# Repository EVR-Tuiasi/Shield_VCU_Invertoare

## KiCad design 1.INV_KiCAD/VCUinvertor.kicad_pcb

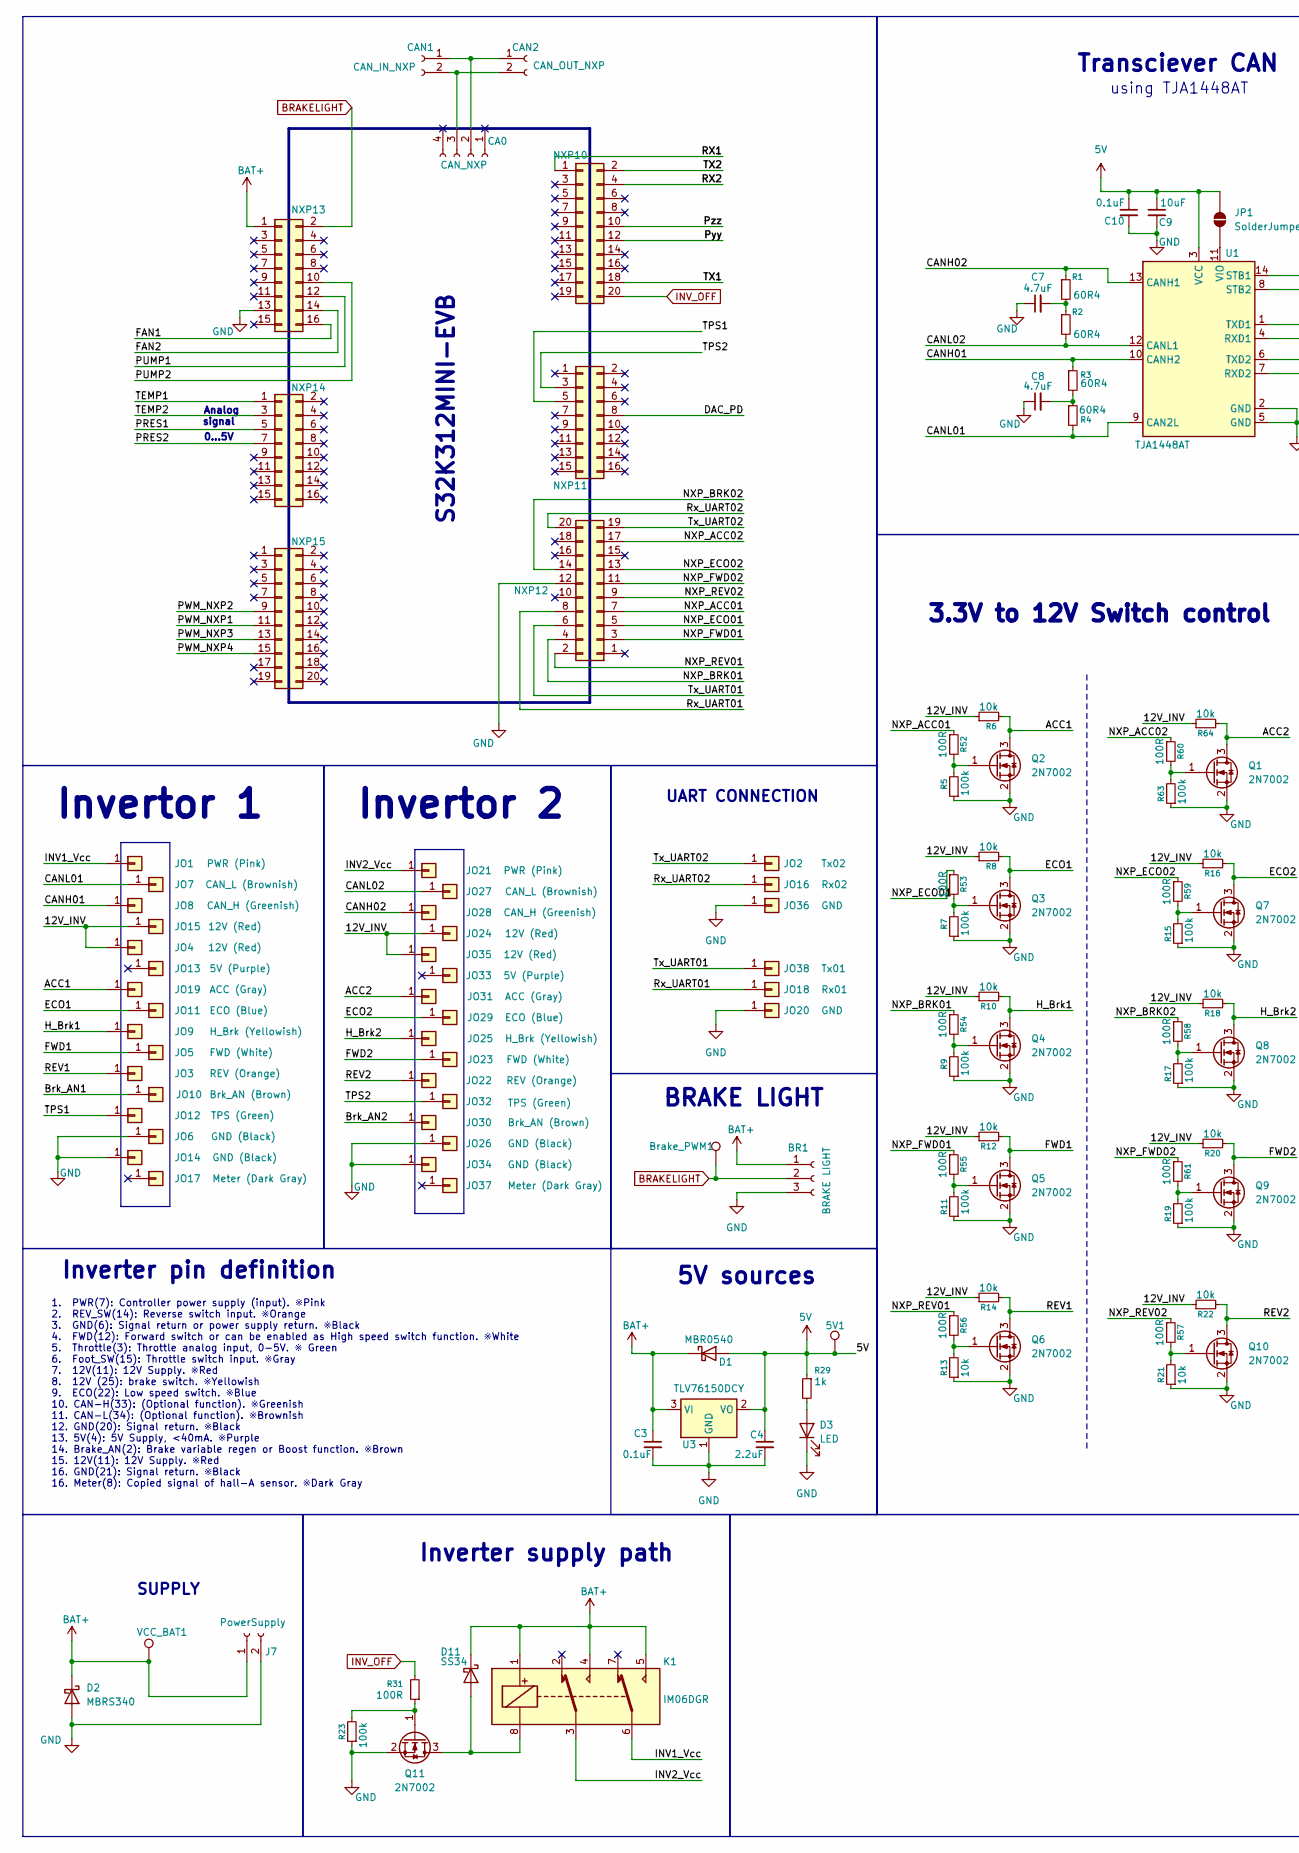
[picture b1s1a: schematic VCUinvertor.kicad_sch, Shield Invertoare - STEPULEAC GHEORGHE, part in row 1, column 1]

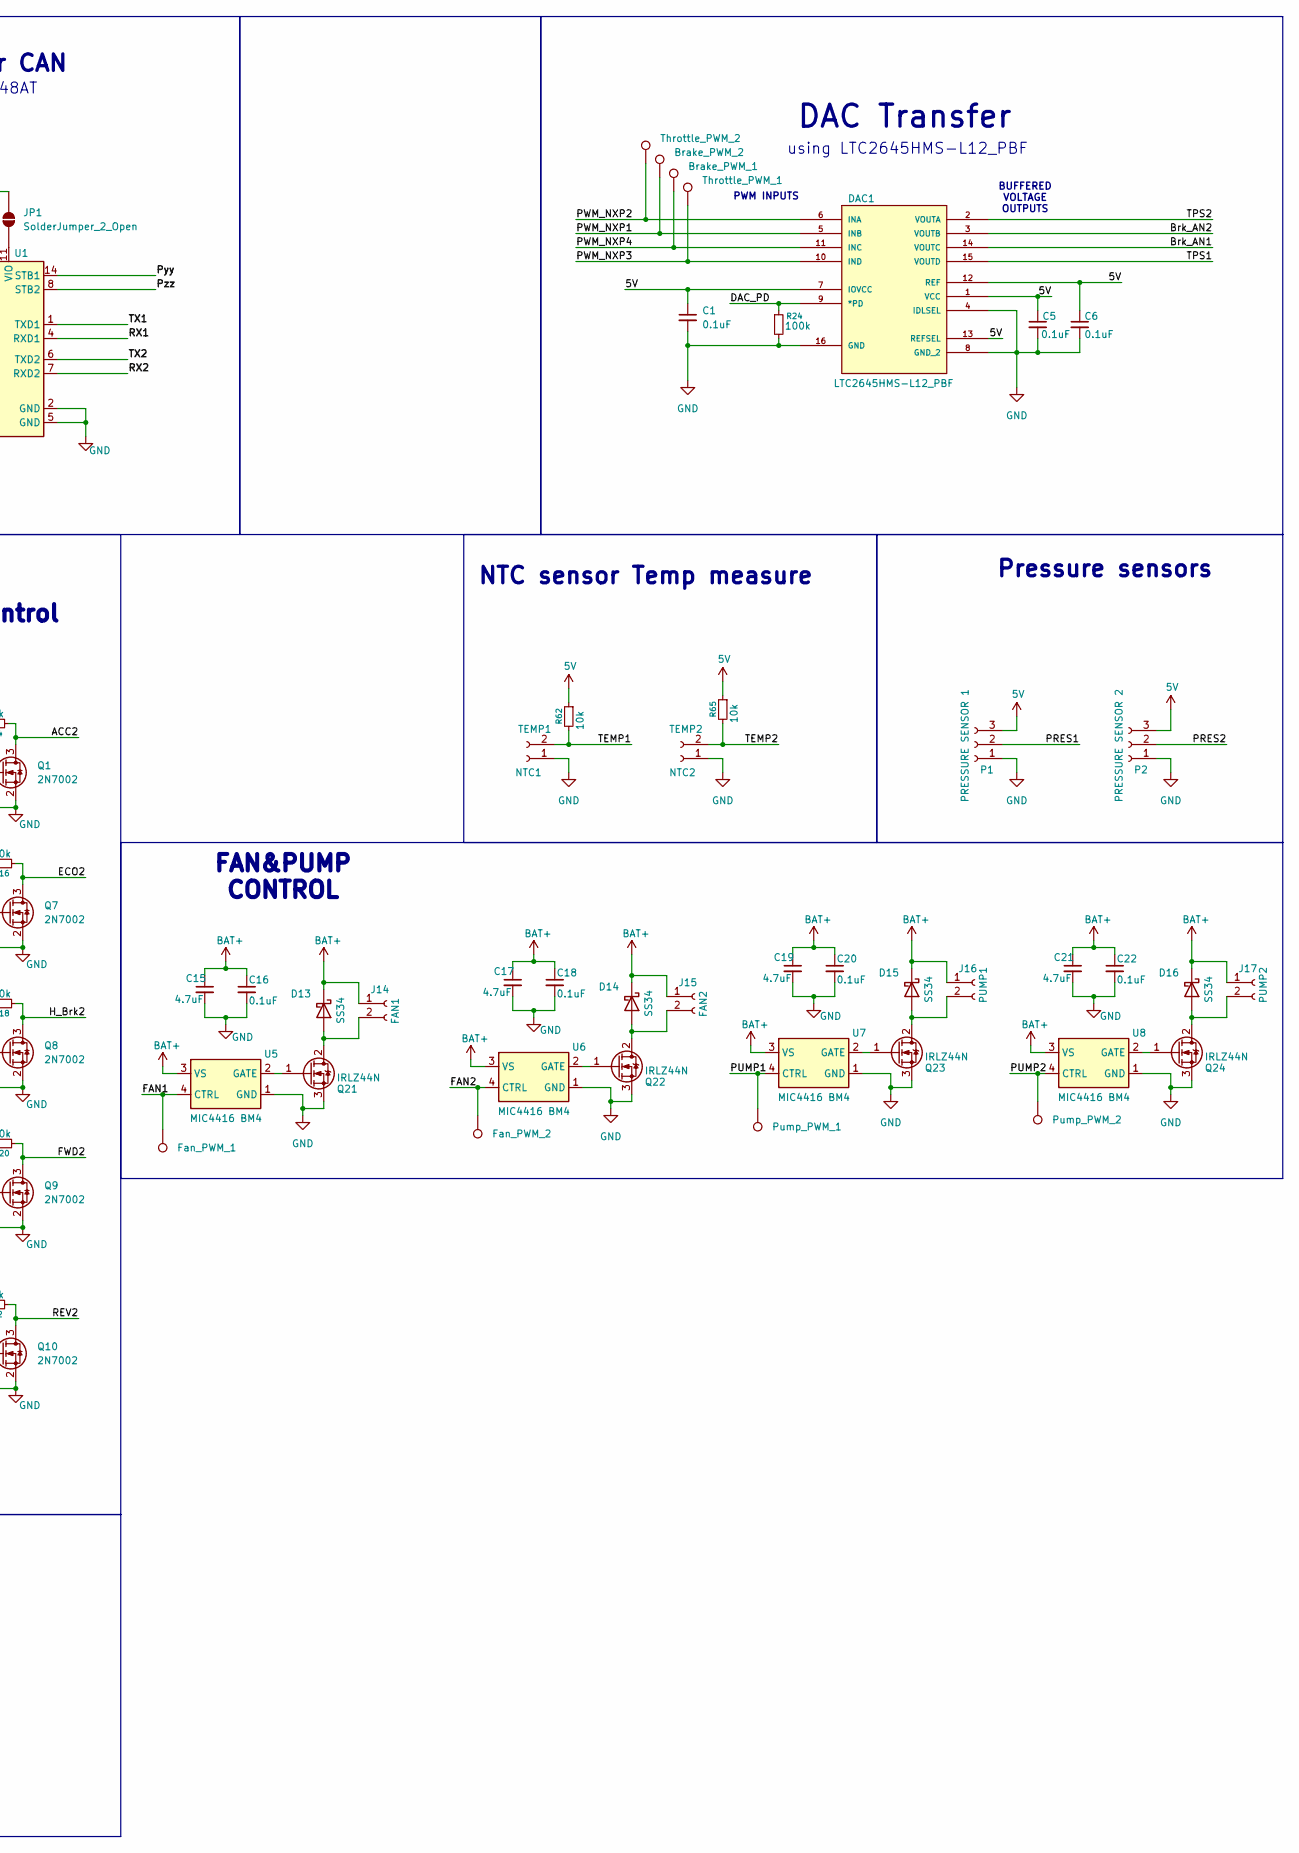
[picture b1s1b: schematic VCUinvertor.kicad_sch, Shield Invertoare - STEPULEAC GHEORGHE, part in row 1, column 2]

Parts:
5V1: 5V; TestPoint_Pad_D1.5mm
BR1: BRAKE LIGHT; JST_XH_B3B-XH-A_1x03_P2.50mm_Vertical
Brake_PWM1: TestPoint; TestPoint_Pad_D1.5mm
Brake_PWM_1, Brake_PWM_2: TestPoint; TestPoint_Pad_D1.5mm
C1, C3, C5, C6, C10, C16, C18, C20, C22: 0.1uF; C_1206_3216Metric_Pad1.33x1.80mm_HandSolder
C4: 2.2uF; C_1206_3216Metric_Pad1.33x1.80mm_HandSolder
C7, C8, C15, C17, C19, C21: 4.7uF; C_1206_3216Metric_Pad1.33x1.80mm_HandSolder
C9: 10uF; C_1206_3216Metric_Pad1.33x1.80mm_HandSolder
CA0: CAN_NXP; PinHeader_1x04_P2.54mm_Vertical
CAN1: CAN_IN_NXP; JST_PH_B2B-PH-K_1x02_P2.00mm_Vertical
CAN2: CAN_OUT_NXP; JST_PH_B2B-PH-K_1x02_P2.00mm_Vertical
D1: MBR0540; D_SOD-123
D2: MBRS340; D_SMC
D3: LED; LED_0805_2012Metric_Pad1.15x1.40mm_HandSolder
D11, D13, D14, D15, D16: SS34; D_SMA
DAC1: LTC2645HMS-L12_PBF; MSOP-16_MS; MANUFACTURER_PART_NUMBER ltc2645imsl8#pbf
Fan_PWM_1, Fan_PWM_2: TestPoint; TestPoint_Pad_D1.5mm
J7: PowerSupply; PhoenixContact_GMSTBVA_2,5_2-G-7,62_1x02_P7.62mm_Vertical
J14: FAN1; JST_XH_B2B-XH-A_1x02_P2.50mm_Vertical
J15: FAN2; JST_XH_B2B-XH-A_1x02_P2.50mm_Vertical
J16: PUMP1; JST_XH_B2B-XH-A_1x02_P2.50mm_Vertical
J17: PUMP2; JST_XH_B2B-XH-A_1x02_P2.50mm_Vertical
JO1, JO21: PWR (Pink); SolderWire-0.75sqmm_1x01_D1.25mm_OD2.3mm
JO2: Tx02; SolderWire-0.5sqmm_1x01_D0.9mm_OD2.1mm
JO3, JO22: REV (Orange); SolderWire-0.75sqmm_1x01_D1.25mm_OD2.3mm
JO4, JO15, JO24, JO35: 12V (Red); SolderWire-0.75sqmm_1x01_D1.25mm_OD2.3mm
JO5, JO23: FWD (White); SolderWire-0.75sqmm_1x01_D1.25mm_OD2.3mm
JO6, JO14, JO26, JO34: GND (Black); SolderWire-0.75sqmm_1x01_D1.25mm_OD2.3mm
JO7, JO27: CAN_L (Brownish); SolderWire-0.75sqmm_1x01_D1.25mm_OD2.3mm
JO8, JO28: CAN_H (Greenish); SolderWire-0.75sqmm_1x01_D1.25mm_OD2.3mm
JO9, JO25: H_Brk (Yellowish); SolderWire-0.75sqmm_1x01_D1.25mm_OD2.3mm
JO10, JO30: Brk_AN (Brown); SolderWire-0.75sqmm_1x01_D1.25mm_OD2.3mm
JO11, JO29: ECO (Blue); SolderWire-0.75sqmm_1x01_D1.25mm_OD2.3mm
JO12, JO32: TPS (Green); SolderWire-0.75sqmm_1x01_D1.25mm_OD2.3mm
JO13, JO33: 5V (Purple); SolderWire-0.75sqmm_1x01_D1.25mm_OD2.3mm
JO16: Rx02; SolderWire-0.5sqmm_1x01_D0.9mm_OD2.1mm
JO17, JO37: Meter (Dark Gray); SolderWire-0.75sqmm_1x01_D1.25mm_OD2.3mm
JO18: Rx01; SolderWire-0.5sqmm_1x01_D0.9mm_OD2.1mm
JO19, JO31: ACC (Gray); SolderWire-0.75sqmm_1x01_D1.25mm_OD2.3mm
JO20, JO36: GND; SolderWire-0.5sqmm_1x01_D0.9mm_OD2.1mm
JO38: Tx01; SolderWire-0.5sqmm_1x01_D0.9mm_OD2.1mm
JP1: SolderJumper_2_Open; SolderJumper-2_P1.3mm_Open_RoundedPad1.0x1.5mm
K1: IM06DGR; Relay_IM06DGR
NXP10: NXP10; PinHeader_2x10_P2.54mm_Vertical
NXP11: NXP11; PinHeader_2x08_P2.54mm_Vertical
NXP12: NXP12; PinHeader_2x10_P2.54mm_Vertical
NXP13: NXP13; PinHeader_2x08_P2.54mm_Vertical
NXP14: NXP14; PinHeader_2x08_P2.54mm_Vertical
NXP15: NXP15; PinHeader_2x10_P2.54mm_Vertical
P1: PRESSURE SENSOR 1; JST_PH_B3B-PH-K_1x03_P2.00mm_Vertical
P2: PRESSURE SENSOR 2; JST_PH_B3B-PH-K_1x03_P2.00mm_Vertical
Pump_PWM_1, Pump_PWM_2: TestPoint; TestPoint_Pad_D1.5mm
Q1, Q2, Q3, Q4, Q5, Q6, Q7, Q8, Q9, Q10, Q11: 2N7002; SOT-23
Q21, Q22, Q23, Q24: IRLZ44N; TO-220-3_Vertical
R1, R2, R3, R4: 60R4; R_1206_3216Metric_Pad1.30x1.75mm_HandSolder
R5, R7, R9, R11, R15, R17, R19, R23, R24, R63: 100k; R_1206_3216Metric_Pad1.30x1.75mm_HandSolder
R6, R8, R10, R12, R13, R14, R16, R18, R20, R21, R22, R62, R64, R65: 10k; R_1206_3216Metric_Pad1.30x1.75mm_HandSolder
R29: 1k; R_1206_3216Metric_Pad1.30x1.75mm_HandSolder
R31, R52, R53, R54, R55, R56, R57, R58, R59, R60, R61: 100R; R_1206_3216Metric_Pad1.30x1.75mm_HandSolder
TEMP1: NTC1; JST_PH_B2B-PH-K_1x02_P2.00mm_Vertical
TEMP2: NTC2; JST_PH_B2B-PH-K_1x02_P2.00mm_Vertical
Throttle_PWM_1, Throttle_PWM_2: TestPoint; TestPoint_Pad_D1.5mm
U1: TJA1448AT; NXP-TJA1448A_NXP
U3: TLV76150DCY; SOT-223-3_TabPin2
U5, U6, U7, U8: MIC4416 BM4; SOT-143_Handsoldering
VCC_BAT1: 12V; TestPoint_Pad_D1.5mm

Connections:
5V: 5V1.1 (1_1), C1.1, C4.1, C5.1, C6.1, C9.1, C10.1, D1.2 (A), DAC1.1 (VCC), DAC1.7 (IOVCC), DAC1.12 (REF), DAC1.13 (REFSEL), JP1.2 (B), P1.3, P2.3, R29.1, R62.1, R65.1, U1.3 (VCC), U3.2 (VO)
/12V_INV: JO4.1 (Pin_1_1), JO15.1 (Pin_1_1), JO24.1 (Pin_1_1), JO35.1 (Pin_1_1), R6.1, R8.1, R10.1, R12.1, R14.1, R16.1, R18.1, R20.1, R22.1, R64.1
/ACC1: JO19.1 (Pin_1_1), Q2.3 (D), R6.2
/ACC2: JO31.1 (Pin_1_1), Q1.3 (D), R64.2
/Brk_AN1: DAC1.14 (VOUTC), JO10.1 (Pin_1_1)
/Brk_AN2: DAC1.3 (VOUTB), JO30.1 (Pin_1_1)
/CANH01: JO8.1 (Pin_1_1), R3.1, U1.10 (CANH2)
/CANH02: JO28.1 (Pin_1_1), R1.1, U1.13 (CANH1)
/CANL01: JO7.1 (Pin_1_1), R4.2, U1.9 (CAN2L)
/CANL02: JO27.1 (Pin_1_1), R2.2, U1.12 (CANL1)
/DAC_PD: DAC1.9 (*PD), NXP11.8, R24.1
/ECO1: JO11.1 (Pin_1_1), Q3.3 (D), R8.2
/ECO2: JO29.1 (Pin_1_1), Q7.3 (D), R16.2
/FAN1: Fan_PWM_1.1 (1_1), NXP13.16, U5.4 (CTRL)
/FAN2: Fan_PWM_2.1 (1_1), NXP13.14, U6.4 (CTRL)
/FWD1: JO5.1 (Pin_1_1), Q5.3 (D), R12.2
/FWD2: JO23.1 (Pin_1_1), Q9.3 (D), R20.2
/H_Brk1: JO9.1 (Pin_1_1), Q4.3 (D), R10.2
/H_Brk2: JO25.1 (Pin_1_1), Q8.3 (D), R18.2
/INV1_Vcc: JO1.1 (Pin_1_1), K1.6
/INV2_Vcc: JO21.1 (Pin_1_1), K1.3
/NXP_ACC01: NXP12.7, R52.1
/NXP_ACC02: NXP12.17, R60.1
/NXP_BRK01: NXP12.4, R54.1
/NXP_BRK02: NXP12.14, R58.1
/NXP_ECO01: NXP12.5, R53.1
/NXP_ECO02: NXP12.13, R59.1
/NXP_FWD01: NXP12.3, R55.1
/NXP_FWD02: NXP12.11, R61.1
/NXP_REV01: NXP12.2, R56.1
/NXP_REV02: NXP12.9, R57.1
/PRES1: NXP14.5, P1.2
/PRES2: NXP14.7, P2.2
/PUMP1: NXP13.12, Pump_PWM_1.1 (1_1), U7.4 (CTRL)
/PUMP2: NXP13.10, Pump_PWM_2.1 (1_1), U8.4 (CTRL)
/PWM_NXP1: Brake_PWM_2.1 (1_1), DAC1.5 (INB), NXP15.11
/PWM_NXP2: DAC1.6 (INA), NXP15.9, Throttle_PWM_2.1 (1_1)
/PWM_NXP3: DAC1.10 (IND), NXP15.13, Throttle_PWM_1.1 (1_1)
/PWM_NXP4: Brake_PWM_1.1 (1_1), DAC1.11 (INC), NXP15.15
/Pyy: NXP10.12, U1.14 (STB1)
/Pzz: NXP10.10, U1.8 (STB2)
/REV1: JO3.1 (Pin_1_1), Q6.3 (D), R14.2
/REV2: JO22.1 (Pin_1_1), Q10.3 (D), R22.2
/RX1: NXP10.1, U1.4 (RXD1)
/RX2: NXP10.4, U1.7 (RXD2)
/Rx_UART01: JO18.1 (Pin_1_1), NXP12.8
/Rx_UART02: JO16.1 (Pin_1_1), NXP12.20
/TEMP1: NXP14.1, R62.2, TEMP1.2
/TEMP2: NXP14.3, R65.2, TEMP2.2
/TPS1: DAC1.15 (VOUTD), JO12.1 (Pin_1_1), NXP11.5
/TPS2: DAC1.2 (VOUTA), JO32.1 (Pin_1_1), NXP11.3
/TX1: NXP10.18, U1.1 (TXD1)
/TX2: NXP10.2, U1.6 (TXD2)
/Tx_UART01: JO38.1 (Pin_1_1), NXP12.6
/Tx_UART02: JO2.1 (Pin_1_1), NXP12.19
BAT+: BR1.1, C3.1, C15.1, C16.1, C17.1, C18.1, C19.1, C20.1, C21.1, C22.1, D1.1 (K), D2.1 (K), D11.1 (K), D13.1 (K), D14.1 (K), D15.1 (K), D16.1 (K), J7.1, J14.1, J15.1, J16.1, J17.1, K1.1, K1.4, K1.5, NXP13.1, U3.3 (VI), U5.3 (VS), U6.3 (VS), U7.3 (VS), U8.3 (VS), VCC_BAT1.1 (1_1)
BRAKELIGHT: BR1.2, Brake_PWM1.1 (1_1), NXP13.2
GND: BR1.3, C1.2, C3.2, C4.2, C5.2, C6.2, C7.1, C8.1, C9.2, C10.2, C15.2, C16.2, C17.2, C18.2, C19.2, C20.2, C21.2, C22.2, D2.2 (A), D3.1 (K), DAC1.4 (IDLSEL), DAC1.8 (GND_2), DAC1.16 (GND), J7.2, JO6.1 (Pin_1_1), JO14.1 (Pin_1_1), JO20.1 (Pin_1_1), JO26.1 (Pin_1_1), JO34.1 (Pin_1_1), JO36.1 (Pin_1_1), NXP12.12, NXP13.13, P1.1, P2.1, Q1.2 (S), Q2.2 (S), Q3.2 (S), Q4.2 (S), Q5.2 (S), Q6.2 (S), Q7.2 (S), Q8.2 (S), Q9.2 (S), Q10.2 (S), Q11.2 (S), Q21.3 (S), Q22.3 (S), Q23.3 (S), Q24.3 (S), R5.1, R7.1, R9.1, R11.1, R13.1, R15.1, R17.1, R19.1, R21.1, R23.1, R24.2, R63.1, TEMP1.1, TEMP2.1, U1.2 (GND), U1.5 (GND), U3.1 (GND), U5.1 (GND), U6.1 (GND), U7.1 (GND), U8.1 (GND)
INV_OFF: NXP10.20, R31.2
unnamed: C7.2, R1.2, R2.1
unnamed: C8.2, R3.2, R4.1
unnamed: CA0.2, CAN1.1, CAN2.1
unnamed: CA0.3, CAN1.2, CAN2.2
unnamed: D3.2 (A), R29.2
unnamed: D11.2 (A), K1.8, Q11.3 (D)
unnamed: D13.2 (A), J14.2, Q21.2 (D)
unnamed: D14.2 (A), J15.2, Q22.2 (D)
unnamed: D15.2 (A), J16.2, Q23.2 (D)
unnamed: D16.2 (A), J17.2, Q24.2 (D)
unnamed: JP1.1 (A), U1.11 (VIO)
unnamed: Q1.1 (G), R60.2, R63.2
unnamed: Q2.1 (G), R5.2, R52.2
unnamed: Q3.1 (G), R7.2, R53.2
unnamed: Q4.1 (G), R9.2, R54.2
unnamed: Q5.1 (G), R11.2, R55.2
unnamed: Q6.1 (G), R13.2, R56.2
unnamed: Q7.1 (G), R15.2, R59.2
unnamed: Q8.1 (G), R17.2, R58.2
unnamed: Q9.1 (G), R19.2, R61.2
unnamed: Q10.1 (G), R21.2, R57.2
unnamed: Q11.1 (G), R23.2, R31.1
unnamed: Q21.1 (G), U5.2 (GATE)
unnamed: Q22.1 (G), U6.2 (GATE)
unnamed: Q23.1 (G), U7.2 (GATE)
unnamed: Q24.1 (G), U8.2 (GATE)

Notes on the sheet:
Transciever CAN
using LTC2645HMS-L12_PBF
NTC sensor Temp measure
UART CONNECTION
SUPPLY
FAN&PUMP CONTROL
3.3V to 12V Switch control
PWM INPUTS
BUFFERED VOLTAGE OUTPUTS
0...5V
Invertor 1
S32K312MINI-EVB
1. PWR(7): Controller power supply (input). ※Pink 2. REV_SW(14): Reverse switch input. ※Orange 3. GND(6): Signal return or power supply return. ※Black 4. FWD(12): Forward switch or can be enabled as High speed switch function. ※White 5. Throttle(3): Throttle analog input, 0-5V. ※ Green 6. Foot_SW(1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
Analog signal
Inverter supply path
Invertor 2
using TJA1448AT
Pressure sensors
5V sources
DAC Transfer
BRAKE LIGHT
Inverter pin definition

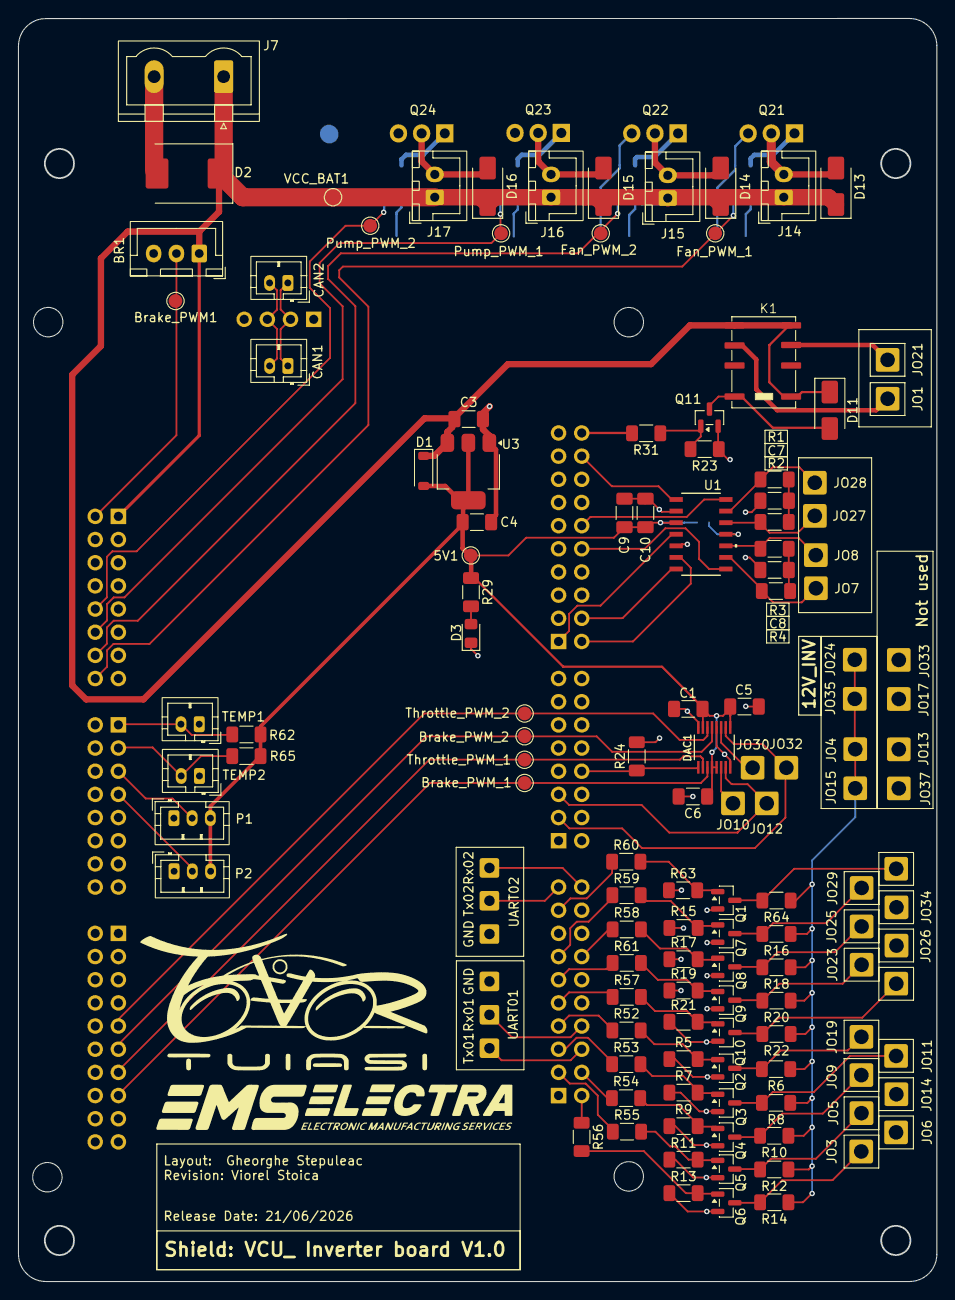
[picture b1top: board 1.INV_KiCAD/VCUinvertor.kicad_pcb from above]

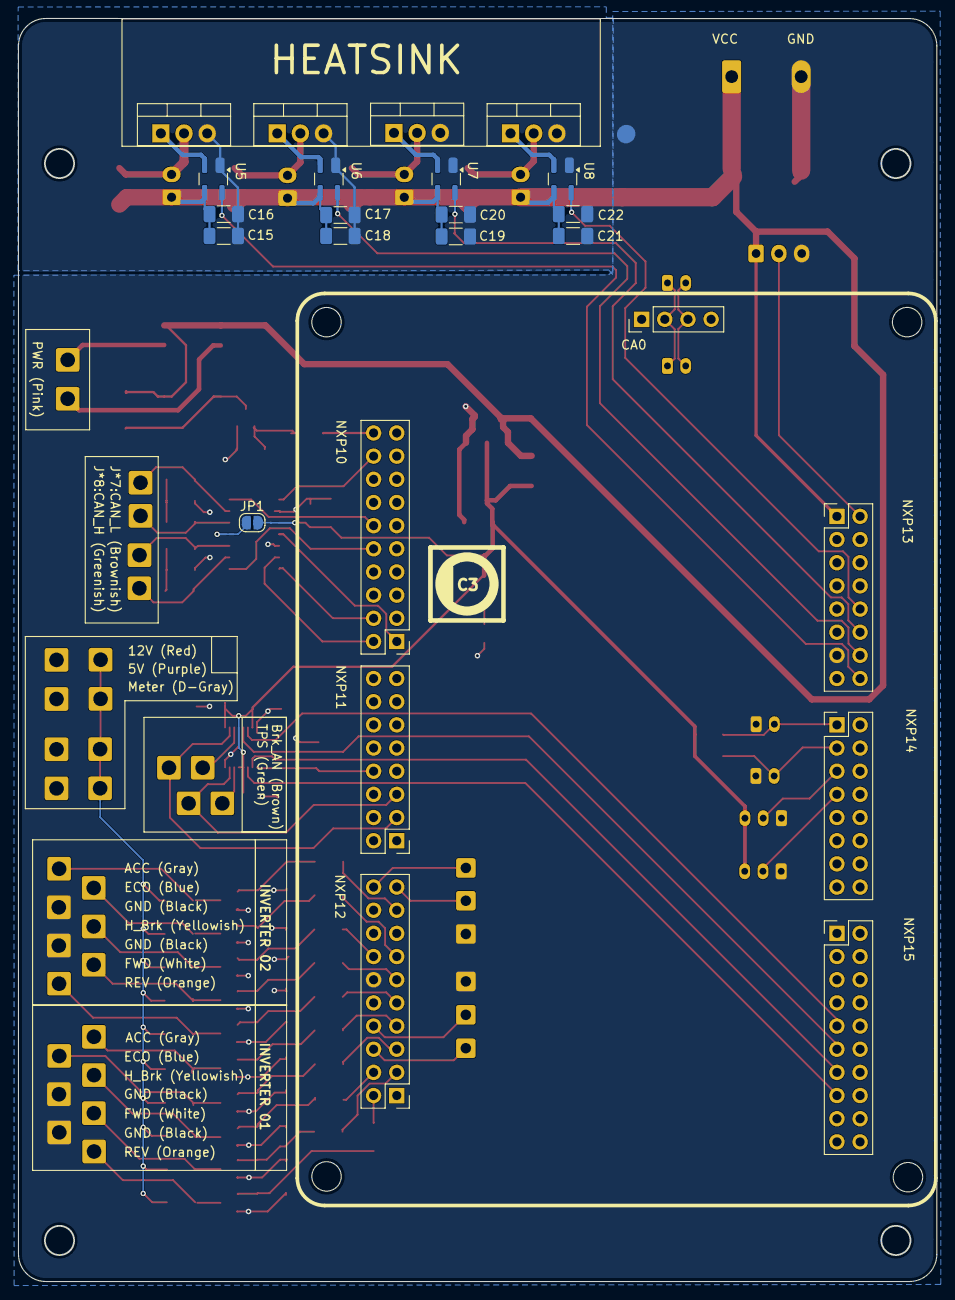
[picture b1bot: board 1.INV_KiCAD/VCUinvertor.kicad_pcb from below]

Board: 2 copper layers, 100.5 x 138.3 mm, 157 parts (24 on the bottom side), 85 nets.

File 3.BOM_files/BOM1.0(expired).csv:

Reference,Qty,Value,DNP,Exclude from BOM,Exclude from Board,Footprint,Datasheet
"C1,C2,C3,C5,C6,C10,C12",7,0.1uF,,,,Capacitor_SMD:C_0805_2012Metric_Pad1.18x1.45mm_HandSolder,~
C4,1,2.2uF,,,,Capacitor_SMD:C_0805_2012Metric_Pad1.18x1.45mm_HandSolder,~
"C7,C8",2,4.7uF,,,,Capacitor_SMD:C_0805_2012Metric_Pad1.18x1.45mm_HandSolder,~
"C9,C11",2,10uF,,,,Capacitor_SMD:C_0805_2012Metric_Pad1.18x1.45mm_HandSolder,~
CA0,1,CAN_NXP,,,,Connector_PinHeader_2.54mm:PinHeader_1x04_P2.54mm_Vertical,~
CA1,1,CAN_OUT_NXP,,,,Connector_JST:JST_PH_B2B-PH-K_1x02_P2.00mm_Vertical,~
D1,1,MBR0540,,,,Diode_SMD:D_SOD-123,http://www.mccsemi.com/up_pdf/MBR0520~MBR0580(SOD123).pdf
D2,1,MBRS340,,,,Diode_SMD:D_SMC,https://www.onsemi.com/download/data-sheet/pdf/mbrs340t3-d.pdf
DAC1,1,LTC2645HMS-L12_PBF,,,,LTC2645HMS-L12_PBF:MSOP-16_MS,
"H1,H2,H3,H4",4,MountingHole_Pad,,Excluded from BOM,,MountingHole:MountingHole_3.2mm_M3_ISO14580_Pad,~
J7,1,PowerSupply,,,,Connector_JST:JST_PH_B2B-PH-K_1x02_P2.00mm_Vertical,~
J9,1,BREAKLIGHT,,,,Connector_JST:JST_PH_B3B-PH-K_1x03_P2.00mm_Vertical,~
"JO1,JO21",2,PWR (Pink),,,,Connector_Wire:SolderWire-0.75sqmm_1x01_D1.25mm_OD2.3mm,~
"JO3,JO22",2,REV (Orange),,,,Connector_Wire:SolderWire-0.75sqmm_1x01_D1.25mm_OD2.3mm,~
"JO4,JO15,JO24,JO35",4,12V (Red),,,,Connector_Wire:SolderWire-0.75sqmm_1x01_D1.25mm_OD2.3mm,~
"JO5,JO23",2,FWD (White),,,,Connector_Wire:SolderWire-0.75sqmm_1x01_D1.25mm_OD2.3mm,~
"JO6,JO14,JO26,JO34",4,GND (Black),,,,Connector_Wire:SolderWire-0.75sqmm_1x01_D1.25mm_OD2.3mm,~
"JO7,JO27",2,CAN_L (Brownish),,,,Connector_Wire:SolderWire-0.75sqmm_1x01_D1.25mm_OD2.3mm,~
"JO8,JO28",2,CAN_H (Greenish),,,,Connector_Wire:SolderWire-0.75sqmm_1x01_D1.25mm_OD2.3mm,~
"JO9,JO25",2,H_Brk (Yellowish),,,,Connector_Wire:SolderWire-0.75sqmm_1x01_D1.25mm_OD2.3mm,~
"JO10,JO30",2,Brk_AN (Brown),,,,Connector_Wire:SolderWire-0.75sqmm_1x01_D1.25mm_OD2.3mm,~
"JO11,JO29",2,ECO (Blue),,,,Connector_Wire:SolderWire-0.75sqmm_1x01_D1.25mm_OD2.3mm,~
"JO12,JO32",2,TPS (Green),,,,Connector_Wire:SolderWire-0.75sqmm_1x01_D1.25mm_OD2.3mm,~
"JO13,JO33",2,5V (Purple),,,,Connector_Wire:SolderWire-0.75sqmm_1x01_D1.25mm_OD2.3mm,~
"JO19,JO31",2,ACC (Gray),,,,Connector_Wire:SolderWire-0.75sqmm_1x01_D1.25mm_OD2.3mm,~
JU1,1,UART_INV01,,,,Connector_JST:JST_GH_SM04B-GHS-TB_1x04-1MP_P1.25mm_Horizontal,~
JU2,1,UART_INV02,,,,Connector_JST:JST_GH_SM04B-GHS-TB_1x04-1MP_P1.25mm_Horizontal,~
NXP10,1,NXP10,,,,Connector_PinHeader_2.54mm:PinHeader_2x10_P2.54mm_Vertical,~
NXP11,1,NXP11,,,,Connector_PinHeader_2.54mm:PinHeader_2x08_P2.54mm_Vertical,~
NXP12,1,NXP12,,,,Connector_PinHeader_2.54mm:PinHeader_2x10_P2.54mm_Vertical,~
NXP13,1,NXP13,,,,Connector_PinHeader_2.54mm:PinHeader_2x08_P2.54mm_Vertical,~
NXP14,1,NXP14,,,,Connector_PinHeader_2.54mm:PinHeader_2x08_P2.54mm_Vertical,~
NXP15,1,NXP15,,,,Connector_PinHeader_2.54mm:PinHeader_2x10_P2.54mm_Vertical,~
"Q1,Q2,Q3,Q4,Q5,Q6,Q7,Q8,Q9,Q10",10,2N7002,,,,Package_TO_SOT_SMD:SOT-23,https://www.onsemi.com/pub/Collateral/NDS7002A-D.PDF
Q11,1,BC848C,,,,Package_TO_SOT_SMD:SOT-23,http://www.infineon.com/dgdl/Infineon-BC847SERIES_BC848SERIE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
Q12,1,BCP51,,,,Package_TO_SOT_SMD:SOT-223-3_TabPin2,https://www.onsemi.com/pub/Collateral/BCP51-D.pdf
"R1,R2,R3,R4",4,60R4,,,,Resistor_SMD:R_0805_2012Metric,~
"R5,R6,R7,R8,R9,R10,R11,R12,R13,R14,R15,R16,R17,R18,R19,R20,R21,R22,R26,R28,R63,R64",22,10k,,,,Resistor_SMD:R_0805_2012Metric,~
R23,1,1.7k,,,,Resistor_SMD:R_0805_2012Metric,~
R24,1,360R,,,,Resistor_SMD:R_0805_2012Metric,~
"R25,R27",2,5.1k,,,,Resistor_SMD:R_0805_2012Metric,~
U1,1,TJA1448ATK,,,,Package_DFN_QFN:DFN-14-1EP_3x4.5mm_P0.65mm_EP1.65x4.25mm,https://www.nxp.com/docs/en/data-sheet/TJA1145.pdf
U2,1,REF3433T,,,,Package_TO_SOT_SMD:SOT-23-6,https://www.ti.com/lit/ds/symlink/ref35.pdf
U3,1,TLV76150DCY,,,,Package_TO_SOT_SMD:SOT-223-3_TabPin2,https://www.ti.com/lit/ds/symlink/tlv761.pdf

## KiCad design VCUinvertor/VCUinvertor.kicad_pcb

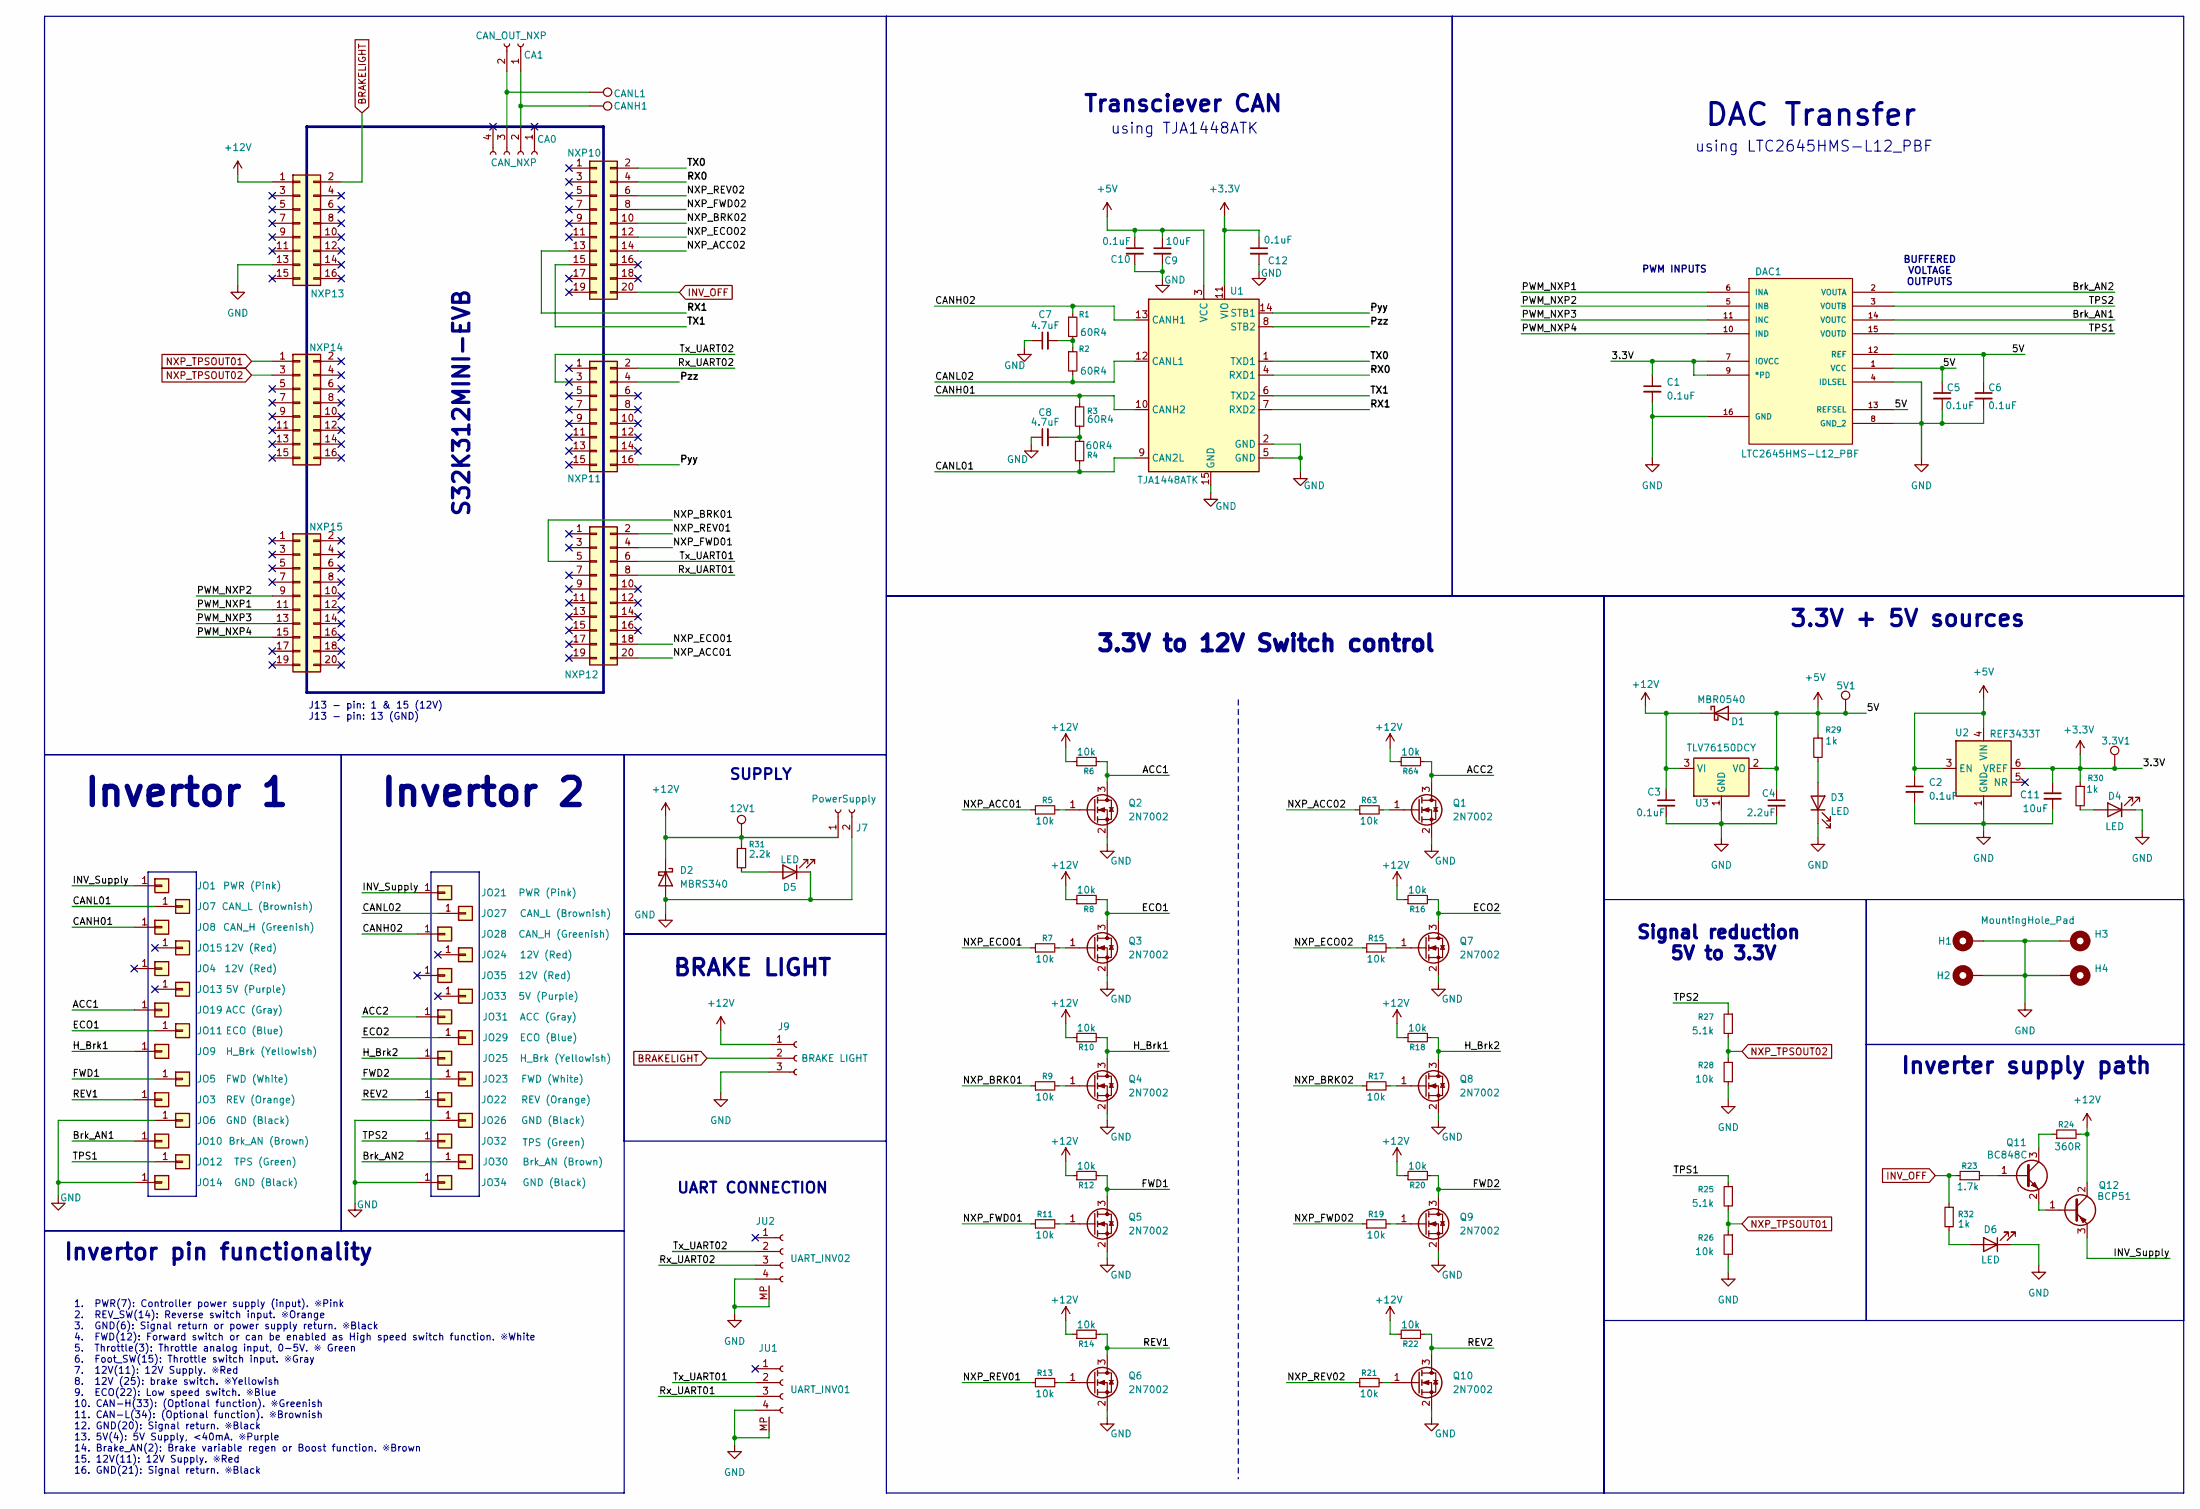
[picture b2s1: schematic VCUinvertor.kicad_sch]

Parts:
3.3V1: 3.3V; TestPoint_Pad_D1.5mm
5V1: 5V; TestPoint_Pad_D1.5mm
12V1: 12V; TestPoint_Pad_D1.5mm
C1, C2, C3, C5, C6, C10, C12: 0.1uF; C_1206_3216Metric_Pad1.33x1.80mm_HandSolder
C4: 2.2uF; C_1206_3216Metric_Pad1.33x1.80mm_HandSolder
C7, C8: 4.7uF; C_1206_3216Metric_Pad1.33x1.80mm_HandSolder
C9, C11: 10uF; C_1206_3216Metric_Pad1.33x1.80mm_HandSolder
CA0: CAN_NXP; PinHeader_1x04_P2.54mm_Vertical
CA1: CAN_OUT_NXP; JST_PH_B2B-PH-K_1x02_P2.00mm_Vertical
CANH1: CANH; TestPoint_Pad_D1.5mm
CANL1: CANL; TestPoint_Pad_D1.5mm
D1: MBR0540; D_SOD-123
D2: MBRS340; D_SMC
D3, D4, D5, D6: LED; LED_0805_2012Metric_Pad1.15x1.40mm_HandSolder
DAC1: LTC2645HMS-L12_PBF; MSOP-16_MS; MANUFACTURER_PART_NUMBER ltc2645imsl8#pbf
H1, H2, H3, H4: MountingHole_Pad; MountingHole_3.2mm_M3_ISO14580_Pad
J7: PowerSupply; JST_PH_B2B-PH-K_1x02_P2.00mm_Vertical
J9: BRAKE LIGHT; JST_PH_B3B-PH-K_1x03_P2.00mm_Vertical
JO1, JO21: PWR (Pink); SolderWire-0.75sqmm_1x01_D1.25mm_OD2.3mm
JO3, JO22: REV (Orange); SolderWire-0.75sqmm_1x01_D1.25mm_OD2.3mm
JO4, JO15, JO24, JO35: 12V (Red); SolderWire-0.75sqmm_1x01_D1.25mm_OD2.3mm
JO5, JO23: FWD (White); SolderWire-0.75sqmm_1x01_D1.25mm_OD2.3mm
JO6, JO14, JO26, JO34: GND (Black); SolderWire-0.75sqmm_1x01_D1.25mm_OD2.3mm
JO7, JO27: CAN_L (Brownish); SolderWire-0.75sqmm_1x01_D1.25mm_OD2.3mm
JO8, JO28: CAN_H (Greenish); SolderWire-0.75sqmm_1x01_D1.25mm_OD2.3mm
JO9, JO25: H_Brk (Yellowish); SolderWire-0.75sqmm_1x01_D1.25mm_OD2.3mm
JO10, JO30: Brk_AN (Brown); SolderWire-0.75sqmm_1x01_D1.25mm_OD2.3mm
JO11, JO29: ECO (Blue); SolderWire-0.75sqmm_1x01_D1.25mm_OD2.3mm
JO12, JO32: TPS (Green); SolderWire-0.75sqmm_1x01_D1.25mm_OD2.3mm
JO13, JO33: 5V (Purple); SolderWire-0.75sqmm_1x01_D1.25mm_OD2.3mm
JO19, JO31: ACC (Gray); SolderWire-0.75sqmm_1x01_D1.25mm_OD2.3mm
JU1: UART_INV01; JST_GH_SM04B-GHS-TB_1x04-1MP_P1.25mm_Horizontal
JU2: UART_INV02; JST_GH_SM04B-GHS-TB_1x04-1MP_P1.25mm_Horizontal
NXP10: NXP10; PinHeader_2x10_P2.54mm_Vertical
NXP11: NXP11; PinHeader_2x08_P2.54mm_Vertical
NXP12: NXP12; PinHeader_2x10_P2.54mm_Vertical
NXP13: NXP13; PinHeader_2x08_P2.54mm_Vertical
NXP14: NXP14; PinHeader_2x08_P2.54mm_Vertical
NXP15: NXP15; PinHeader_2x10_P2.54mm_Vertical
Q1, Q2, Q3, Q4, Q5, Q6, Q7, Q8, Q9, Q10: 2N7002; SOT-23
Q11: BC848C; SOT-23
Q12: BCP51; SOT-223-3_TabPin2
R1, R2, R3, R4: 60R4; R_1206_3216Metric_Pad1.30x1.75mm_HandSolder
R5, R6, R7, R8, R9, R10, R11, R12, R13, R14, R15, R16, R17, R18, R19, R20, R21, R22, R26, R63, R64: 10k; R_1206_3216Metric_Pad1.30x1.75mm_HandSolder
R23: 1.7k; R_1206_3216Metric_Pad1.30x1.75mm_HandSolder
R24: 360R; R_1206_3216Metric_Pad1.30x1.75mm_HandSolder
R25: 5.1k; R_1206_3216Metric_Pad1.30x1.75mm_HandSolder
R27: 5.1k; R_0805_2012Metric
R28: 10k; R_0805_2012Metric
R29, R30, R32: 1k; R_0805_2012Metric
R31: 2.2k; R_0805_2012Metric
U1: TJA1448ATK; DFN-14-1EP_3x4.5mm_P0.65mm_EP1.65x4.25mm
U2: REF3433T; SOT-23-6
U3: TLV76150DCY; SOT-223-3_TabPin2

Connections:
+3.3V: 3.3V1.1, C1.1, C11.1, C12.1, DAC1.7 (IOVCC), DAC1.9 (*PD), R30.1, U1.11 (VIO), U2.6 (VREF)
+5V: 5V1.1, C2.1, C4.1, C5.1, C6.1, C9.1, C10.1, D1.2 (A), DAC1.1 (VCC), DAC1.12 (REF), DAC1.13 (REFSEL), R29.1, U1.3 (VCC), U2.3 (EN), U2.4 (VIN), U3.2 (VO)
+12V: 12V1.1, C3.1, D1.1 (K), D2.1 (K), J7.1, J9.1, NXP13.1, Q12.2 (C), R6.1, R8.1, R10.1, R12.1, R14.1, R16.1, R18.1, R20.1, R22.1, R24.2, R31.1, R64.1, U3.3 (VI)
/ACC1: JO19.1, Q2.3 (D), R6.2
/ACC2: JO31.1, Q1.3 (D), R64.2
/Brk_AN1: DAC1.14 (VOUTC), JO10.1
/Brk_AN2: DAC1.2 (VOUTA), JO30.1
/CANH01: JO8.1, R3.1, U1.10 (CANH2)
/CANH02: JO28.1, R1.1, U1.13 (CANH1)
/CANL01: JO7.1, R4.2, U1.9 (CAN2L)
/CANL02: JO27.1, R2.2, U1.12 (CANL1)
/ECO1: JO11.1, Q3.3 (D), R8.2
/ECO2: JO29.1, Q7.3 (D), R16.2
/FWD1: JO5.1, Q5.3 (D), R12.2
/FWD2: JO23.1, Q9.3 (D), R20.2
/H_Brk1: JO9.1, Q4.3 (D), R10.2
/H_Brk2: JO25.1, Q8.3 (D), R18.2
/INV_Supply: JO1.1, JO21.1, Q12.3 (E)
/NXP_ACC01: NXP12.20, R5.1
/NXP_ACC02: NXP10.14, R63.1
/NXP_BRK01: NXP12.5, R9.1
/NXP_BRK02: NXP10.10, R17.1
/NXP_ECO01: NXP12.18, R7.1
/NXP_ECO02: NXP10.12, R15.1
/NXP_FWD01: NXP12.4, R11.1
/NXP_FWD02: NXP10.8, R19.1
/NXP_REV01: NXP12.2, R13.1
/NXP_REV02: NXP10.6, R21.1
/PWM_NXP1: DAC1.6 (INA), NXP15.11
/PWM_NXP2: DAC1.5 (INB), NXP15.9
/PWM_NXP3: DAC1.11 (INC), NXP15.13
/PWM_NXP4: DAC1.10 (IND), NXP15.15
/Pyy: NXP11.16, U1.14 (STB1)
/Pzz: NXP11.4, U1.8 (STB2)
/REV1: JO3.1, Q6.3 (D), R14.2
/REV2: JO22.1, Q10.3 (D), R22.2
/RX0: NXP10.4, U1.4 (RXD1)
/RX1: NXP10.13, U1.7 (RXD2)
/Rx_UART01: JU1.3, NXP12.8
/Rx_UART02: JU2.3, NXP11.2
/TPS1: DAC1.15 (VOUTD), JO12.1, R25.1
/TPS2: DAC1.3 (VOUTB), JO32.1, R27.1
/TX0: NXP10.2, U1.1 (TXD1)
/TX1: NXP10.15, U1.6 (TXD2)
/Tx_UART01: JU1.2, NXP12.6
/Tx_UART02: JU2.2, NXP11.3
BRAKELIGHT: J9.2, NXP13.2
GND: C1.2, C2.2, C3.2, C4.2, C5.2, C6.2, C7.1, C8.1, C9.2, C10.2, C11.2, C12.2, D2.2 (A), D3.1 (K), D4.1 (K), D5.1 (K), D6.1 (K), DAC1.4 (IDLSEL), DAC1.8 (GND_2), DAC1.16 (GND), H1.1, H2.1, H3.1, H4.1, J7.2, J9.3, JO6.1, JO14.1, JO26.1, JO34.1, JU1.4, JU1.MP, JU2.4, JU2.MP, NXP13.13, Q1.2 (S), Q2.2 (S), Q3.2 (S), Q4.2 (S), Q5.2 (S), Q6.2 (S), Q7.2 (S), Q8.2 (S), Q9.2 (S), Q10.2 (S), R26.2, R28.2, U1.2 (GND), U1.5 (GND), U1.15 (GND), U2.1 (GND), U2.2 (GND), U3.1 (GND)
INV_OFF: NXP10.20, R23.1, R32.1
NXP_TPSOUT01: NXP14.1, R25.2, R26.1
NXP_TPSOUT02: NXP14.3, R27.2, R28.1
unnamed: C7.2, R1.2, R2.1
unnamed: C8.2, R3.2, R4.1
unnamed: CA0.2, CA1.1, CANH1.1
unnamed: CA0.3, CA1.2, CANL1.1
unnamed: D3.2 (A), R29.2
unnamed: D4.2 (A), R30.2
unnamed: D5.2 (A), R31.2
unnamed: D6.2 (A), R32.2
unnamed: Q1.1 (G), R63.2
unnamed: Q2.1 (G), R5.2
unnamed: Q3.1 (G), R7.2
unnamed: Q4.1 (G), R9.2
unnamed: Q5.1 (G), R11.2
unnamed: Q6.1 (G), R13.2
unnamed: Q7.1 (G), R15.2
unnamed: Q8.1 (G), R17.2
unnamed: Q9.1 (G), R19.2
unnamed: Q10.1 (G), R21.2
unnamed: Q11.1 (B), R23.2
unnamed: Q11.3 (C), R24.1
unnamed: Q11.2 (E), Q12.1 (B)

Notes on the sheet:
Transciever CAN
using LTC2645HMS-L12_PBF
UART CONNECTION
J13 - pin: 1 & 15 (12V) J13 - pin: 13 (GND)
SUPPLY
3.3V to 12V Switch control
PWM INPUTS
Signal reduction 5V to 3.3V
BUFFERED VOLTAGE OUTPUTS
Invertor 1
S32K312MINI-EVB
1. PWR(7): Controller power supply (input). ※Pink 2. REV_SW(14): Reverse switch input. ※Orange 3. GND(6): Signal return or power supply return. ※Black 4. FWD(12): Forward switch or can be enabled as High speed switch function. ※White 5. Throttle(3): Throttle analog input, 0-5V. ※ Green 6. Foot_SW(1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
Inverter supply path
Invertor 2
using TJA1448ATK
3.3V + 5V sources
DAC Transfer
BRAKE LIGHT
Invertor pin functionality
